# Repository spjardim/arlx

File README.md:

# Audio Reactive Lighting eXecutor

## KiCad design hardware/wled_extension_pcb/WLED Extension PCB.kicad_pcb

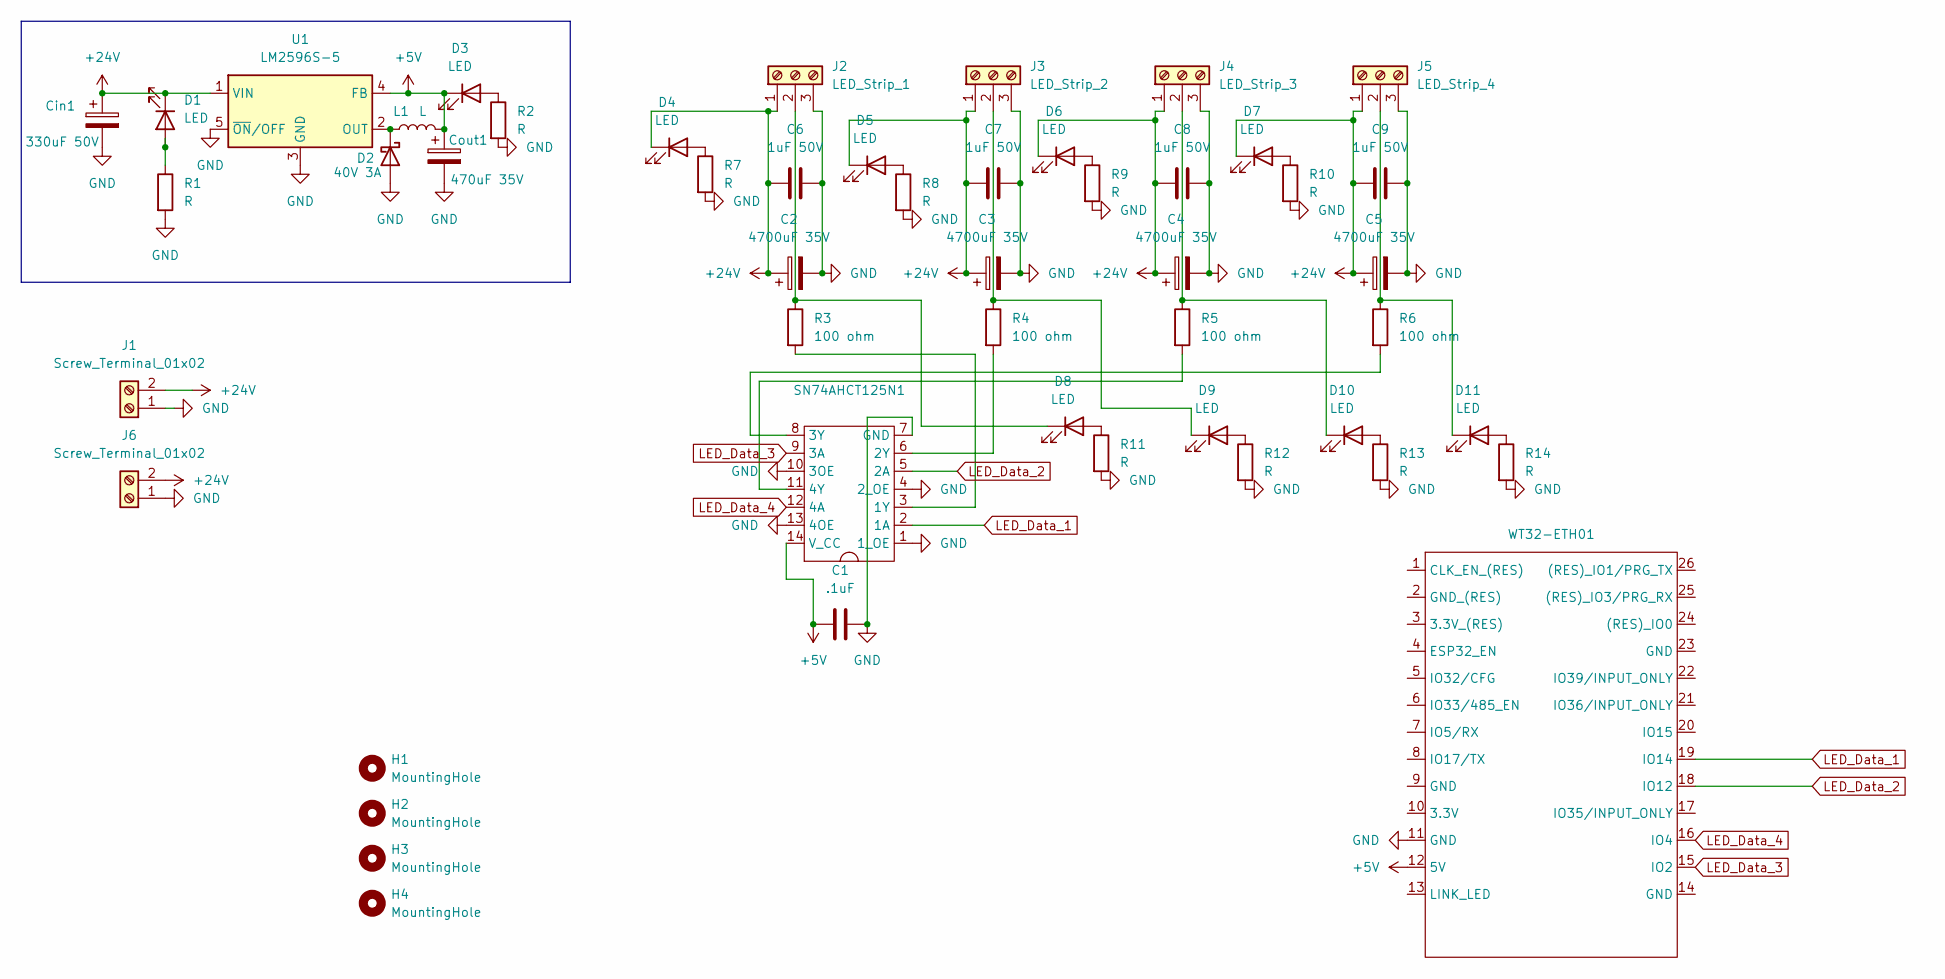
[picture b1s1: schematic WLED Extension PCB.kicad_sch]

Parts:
C1: .1uF; C_Axial_L3.8mm_D2.6mm_P7.50mm_Horizontal
C2, C3, C4, C5: 4700uF 35V; CP_Radial_D10.0mm_P7.50mm
C6, C7, C8, C9: 1uF 50V; C_Axial_L3.8mm_D2.6mm_P7.50mm_Horizontal
Cin1: 330uF 50V; CP_Radial_D10.0mm_P5.00mm
Cout1: 470uF 35V; CP_Radial_D10.0mm_P5.00mm
D1, D3, D4, D5, D6, D7, D8, D9, D10, D11: LED; D_0805_2012Metric_Pad1.15x1.40mm_HandSolder
D2: 40V 3A; D_SMB-SMC_Universal_Handsoldering
H1, H2, H3, H4: MountingHole; MountingHole_3.2mm_M3
J1, J6: Screw_Terminal_01x02; TerminalBlock_MaiXu_MX126-5.0-02P_1x02_P5.00mm
J2: LED_Strip_1; TerminalBlock_MaiXu_MX126-5.0-03P_1x03_P5.00mm
J3: LED_Strip_2; TerminalBlock_MaiXu_MX126-5.0-03P_1x03_P5.00mm
J4: LED_Strip_3; TerminalBlock_MaiXu_MX126-5.0-03P_1x03_P5.00mm
J5: LED_Strip_4; TerminalBlock_MaiXu_MX126-5.0-03P_1x03_P5.00mm
L1: L; Untitled_1
R1, R2, R7, R8, R9, R10, R11, R12, R13, R14: R; R_0805_2012Metric_Pad1.20x1.40mm_HandSolder
R3, R4, R5, R6: 100 ohm; R_0805_2012Metric_Pad1.20x1.40mm_HandSolder
SN74AHCT125N1: DIP-14_W7.62mm
U1: LM2596S-5; TO-263-5_TabPin3
U2: WT32-ETH01

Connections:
+5V: C1.1, Cout1.1, D3.1 (K), L1.2, SN74AHCT125N1.14 (V_CC), U1.4 (FB), U2.12 (5V)
+24V: C2.1, C3.1, C4.1, C5.1, C6.1, C7.1, C8.1, C9.1, Cin1.1, D1.1 (K), D4.1 (K), D5.1 (K), D6.1 (K), D7.1 (K), J1.2, J2.1, J3.1, J4.1, J5.1, J6.2, U1.1 (VIN)
GND: C1.2, C2.2, C3.2, C4.2, C5.2, C6.2, C7.2, C8.2, C9.2, Cin1.2, Cout1.2, D2.2 (A), J1.1, J2.3, J3.3, J4.3, J5.3, J6.1, R1.2, R2.2, R7.2, R8.2, R9.2, R10.2, R11.2, R12.2, R13.2, R14.2, SN74AHCT125N1.1 (1_OE), SN74AHCT125N1.4 (2_OE), SN74AHCT125N1.7 (GND), SN74AHCT125N1.10 (3OE), SN74AHCT125N1.13 (4OE), U1.3 (GND), U1.5 (~ON/OFF), U2.11 (GND)
LED_Data_1: SN74AHCT125N1.2 (1A), U2.19 (IO14)
LED_Data_2: SN74AHCT125N1.5 (2A), U2.18 (IO12)
LED_Data_3: SN74AHCT125N1.9 (3A), U2.15 (IO2)
LED_Data_4: SN74AHCT125N1.12 (4A), U2.16 (IO4)
unnamed: D1.2 (A), R1.1
unnamed: D2.1 (K), L1.1, U1.2 (OUT)
unnamed: D3.2 (A), R2.1
unnamed: D4.2 (A), R7.1
unnamed: D5.2 (A), R8.1
unnamed: D6.2 (A), R9.1
unnamed: D7.2 (A), R10.1
unnamed: D8.2 (A), R11.1
unnamed: D8.1 (K), J2.2, R3.1
unnamed: D9.2 (A), R12.1
unnamed: D9.1 (K), J3.2, R4.1
unnamed: D10.2 (A), R13.1
unnamed: D10.1 (K), J4.2, R5.1
unnamed: D11.2 (A), R14.1
unnamed: D11.1 (K), J5.2, R6.1
unnamed: R3.2, SN74AHCT125N1.3 (1Y)
unnamed: R4.2, SN74AHCT125N1.6 (2Y)
unnamed: R6.2, SN74AHCT125N1.8 (3Y)
unnamed: R5.2, SN74AHCT125N1.11 (4Y)

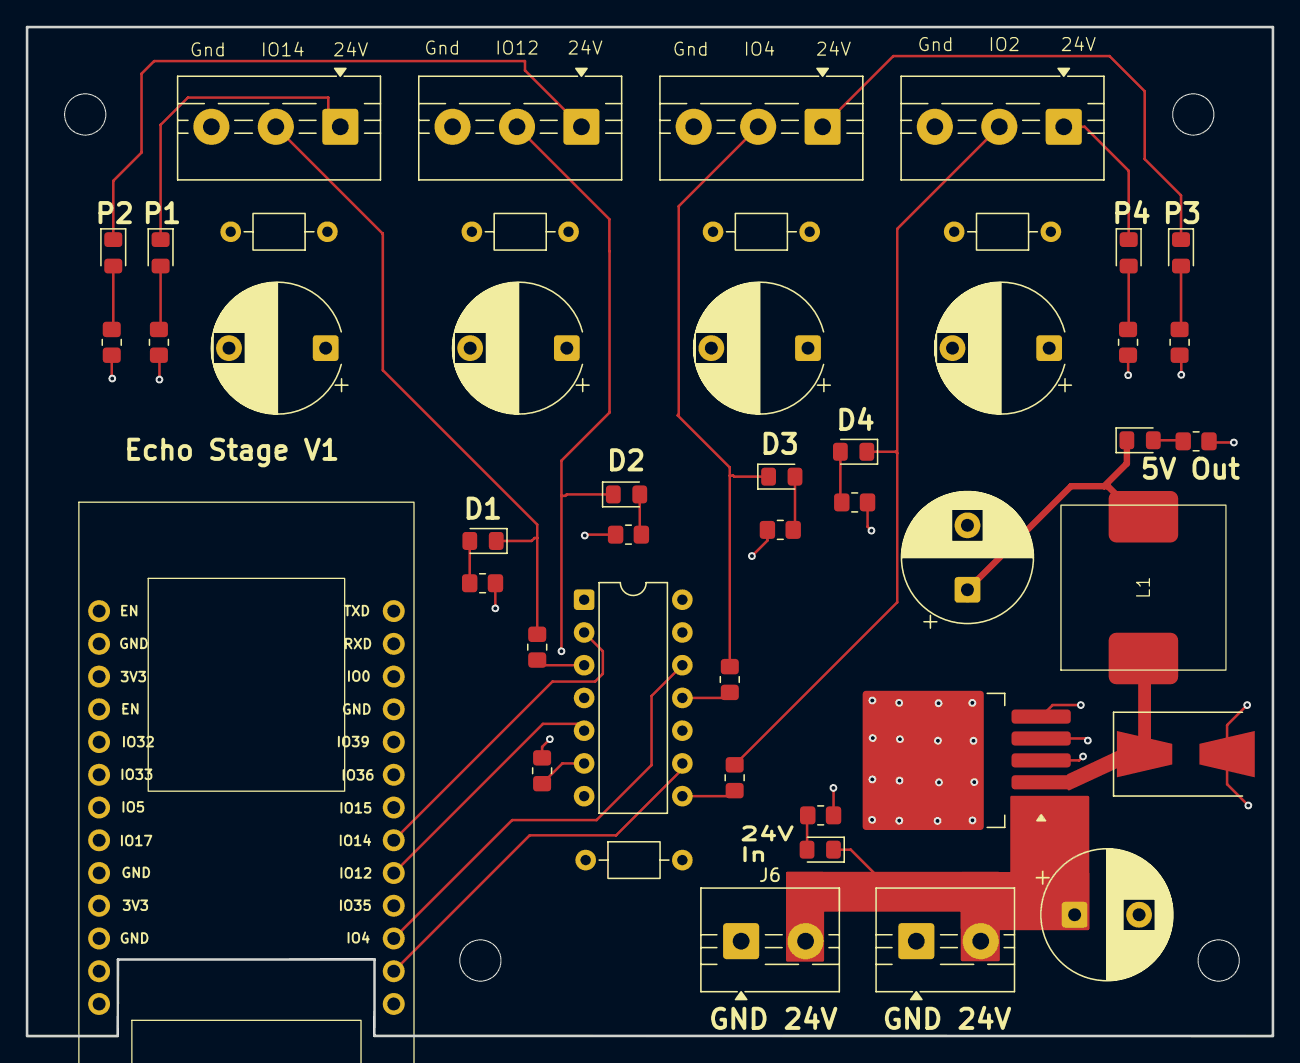
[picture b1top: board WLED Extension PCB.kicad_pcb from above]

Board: 4 copper layers, 96.7 x 78.3 mm, 50 parts (0 on the bottom side), 26 nets.
